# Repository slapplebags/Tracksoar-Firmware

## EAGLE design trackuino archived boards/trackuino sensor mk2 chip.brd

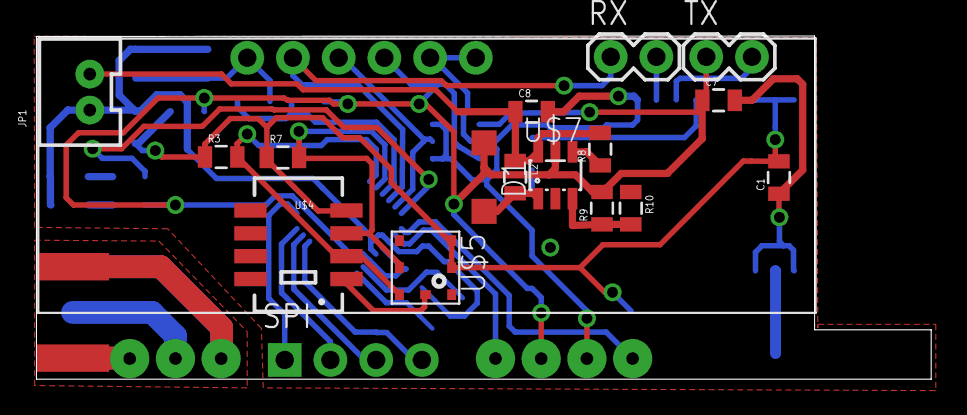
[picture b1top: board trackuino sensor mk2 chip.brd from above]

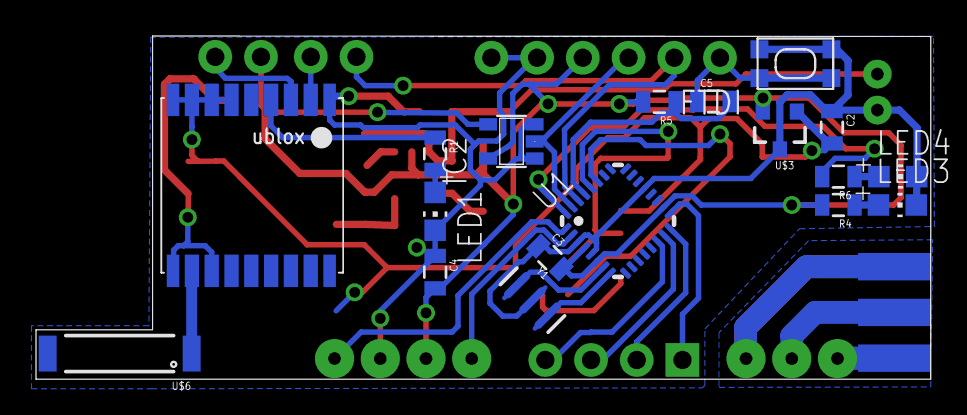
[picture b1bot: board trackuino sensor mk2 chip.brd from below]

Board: 2 copper layers, 49.7 x 19.1 mm, 39 parts (20 on the bottom side), 31 nets.

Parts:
C1, C2, C3, C4, C5, C7, C8: 0805
D1: SOD123
FRAME1: FRAME-LETTER; CREATIVE_COMMONS
FTDI: 1X06_NO_SILK
IC2: 74AHC1G125DBV; SOT23-5
J$1: SMA_EDGE; SMA-EDGE
JP1: M02JST-PTH-VERT; JST-2-PTH-VERT
L2: 0805
LED1, LED3, LED4: CHIP-LED0805
R1, R3, R4, R5, R6, R7, R8, R9, R10: 0805
RX: RX; 1X02
SPI: 1X04_NO_SILK
SW1: SPST_TACT-KMR2; KMR2
TX: TX; 1X02
U1: ATMEGA168MLF; MLF32
U$1: UBLOX_MAX
U$2: RADIOMETRIX-HX1
U$3: LM3480IM4; SOT23-3
U$4: SHT1XSMD; SHT1X
U$5: BMP180
U$6: ANTENNA2SMD3; ANTENNA-CHIP4
U$7: LT3426; SOT23-6
Y1: 16MHZ; RESONATOR-SMD

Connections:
3V: C1.2, C2.2, R3.1, R7.1, U$1.6_V_BCKP, U$1.7_VCC_IO, U$1.8_VCC, U$1.9_V_RESET, U$3.1, U$4.4, U$5.2, U$5.3
15V: C8.1, JP1.2, L2.1, R8.2, U$7.6
D3: U1.1, U$2.TXD
D4: U1.2, U$2.EN
DTR: C5.1, FTDI.1, SW1.1, SW1.3
GND: C1.1, C2.1, C3.1, C4.1, C7.2, C8.2, FTDI.5, FTDI.6, IC2.1, IC2.3, J$1.GND@0, J$1.GND@1, J$1.GND@2, J$1.GND@3, JP1.1, LED1.C, LED3.C, LED4.C, R10.1, SW1.2, SW1.4, U1.3, U1.5, U1.21, U$1.1_GND, U$1.10_GND, U$1.12_GND, U$2.0V, U$2.RFGND, U$2.RFGND2, U$3.3, U$4.1, U$5.7, U$7.2, Y1.2
LED: R6.2, U1.32
MISO: SPI.2, U1.16
MOSI: SPI.3, U1.15
unnamed: J$1.SIG, U$2.RFOUT
unnamed: R1.1, U$1.4_TIMEPULSE
unnamed: LED1.A, R1.2
unnamed: U$1.11_RF_IN, U$6.SIG
unnamed: C5.2, R5.1, U1.29
unnamed: LED3.A, R4.1
unnamed: D1.A, L2.2, U$7.1
unnamed: R8.1, U$7.4
unnamed: R9.1, R10.2, U$7.3
unnamed: U1.8, Y1.3
unnamed: U1.7, Y1.1
unnamed: LED4.A, R6.1
RX: TX.2, U$1.3_RXD1
RXO: FTDI.2, RX.1, U1.30
SCK: SPI.1, U1.17
SCL: R7.2, U1.28, U$4.3, U$5.5
SDA: R3.2, U1.27, U$4.2, U$5.6
SS: SPI.4, U1.14
TX: RX.2, U$1.2_TXD1
TX1: IC2.4, TX.1
TXO: FTDI.3, IC2.2, U1.31
VCC: C3.2, C4.2, C7.1, D1.C, FTDI.4, IC2.5, R4.2, R5.2, R9.2, U1.4, U1.6, U1.18, U$2.VCC, U$3.2, U$7.5

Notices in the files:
parts and their libraries:
SparkFun-PowerIC: Licensing: Creative Commons ShareAlike 4.0 International - https://creativecommons.org/licenses/by-sa/4.0
SparkFun-Aesthetics: Released under the Creative Commons Attribution Share-Alike 4.0 License
SparkFun-Aesthetics: https://creativecommons.org/licenses/by-sa/4.0
